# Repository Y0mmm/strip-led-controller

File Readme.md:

# STM8 RGB LED Strip Controller (Infrared NEC)

Custom low-cost RGB LED strip controller based on STM8, featuring Infrared (NEC protocol) control and perceptually-correct dimming.

## Overview

I bought a Paulmann SimpLED RGB strip to use as a bedside lamp. However, I was not satisfied with its functionalities (RGB light strobes before sleep didn’t make much sense), the colors were too aggressive for my eyes, and the dimming was linear (whereas human vision behaves more like a logarithmic response).

I initially wanted to reflash the original controller, but there were no markings on the IC package. So I decided to rebuild it from scratch.

This redesign addresses those issues with:
- Smooth, perceptually-correct brightness control
- Customizable color profiles
- Infrared remote compatibility (NEC protocol)
- Minimal, low-cost hardware

### Features

- Customizable color mapping
- Smooth, perceptually-correct brightness control
- Customizable color functions (ie: go-to-bed that slowly switch off the lights)
- Drop-in replacement PCB for original enclosure

## Hardware
### PCB Design
The PCB form factor and the position of the power barrel connector are designed to fit into the original controller enclosure and to be powered with the original 12VDC power supply.
I chose to use an STM8S001, as it is inexpensive, low-power, and more than sufficient for this project.

PCB design files are available in the PCB/ directory (KiCad).

### Preview

### Materials
|Name | Value | 	Number	| Comments|
| --- | ----- | ----------- | --------|
|STM8S001J3M3 |	|	1	|https://fr.farnell.com/stmicroelectronics/stm8s001j3m3/mcu-8bit-16mhz-nsoic-8/dp/4036166|
|MC78M05CDTRKG| | 		1|	7805 LDO regulator https://fr.farnell.com/on-semiconductor/mc78m05cdtrkg/regulateur-de-tension/dp/1703354|
|IRLML6344TRPBF	||	3	|N-channel MOSFETs used to control the LEDs https://fr.farnell.com/infineon/irlml6344trpbf/mosfet-canal-n-30v-6-3a-sot23/dp/1857299|
|MJ-179PH|	|	1|	Barrel power connector https://fr.farnell.com/multicomp-pro/mj-179ph/embase-basse-tension-12vdc-4a/dp/1737246|
|TSOP18438	|	|1|	IR receiver (replacement for the original one I broke — this one is actually more powerful) https://fr.farnell.com/vishay/tsop18438/recepteur-ir-24m-0-12mw-m2-lateral/dp/2889952|
|C1|	100 nF	|1|	1608 SMD|
|CVCAP	|1 µF	|1|	1608 SMD|
|R1, R2, R3	|1 kΩ|	3	|Load resistors for the MOSFETs, 1608 SMD|
|R4, R5, R6	|47 kΩ|	3	|Pull-down resistors, 1608 SMD|
|R7, R8, R9	|550 Ω|	3	|Optional load resistors for the LEDs, 1608 SMD|
|R10|	47 kΩ|	1	|Optional pull-down resistor for the JEXT button (not implemented)|
|R11|	1 kΩ	|1|	Load resistor for the optional JEXT button|
|RGB LEDs|	R, G, B|	3|	Optional, for debugging without the LED strip connected, 2012 SMD|
|Pin headers	|	|4	|Used for SWIM programming, IR receiver connection, and LED strip connection|

### IR remote buttons mapping : 

For all the buttons, the NEC Address is `0xef00`. The commands are the following:
| Col A  | Col B  | Col C  | Col D  |
| ------ | ------ | ------ | ------ |
| `0x00` | `0x01` | `0x02` | `0x03` |
| `0x04` | `0x05` | `0x06` | `0x07` |
| `0x08` | `0x09` | `0x0a` | `0x0b` | 
| `0x0c` | `0x0d` | `0x0e` | `0x0f` | 
| `0x10` | `0x11` | `0x12` | `0x13` | 
| `0x14` | `0x15` | `0x16` | `0x17` | 

## Firmware
I wrote the NEC infrared decoder from scratch, mainly for fun. It is built around a finite state machine. The command handler is implemented as a large switch statement.

The firmware is interrupt-driven, aiming to minimize power consumption (although it is not battery-powered).

You can add your own colors in src/config/led_config.c, adjust command codes to match your remote control, and implement additional features.

Since the STM8S001 does not include an FPU, all arithmetic is done using fixed-point math.

I used OpenAI Codex at the end to help refactor parts of the code.

### TODO
Implement features using a button connected to JEXT (e.g., on/off)

### Compile
I use SDCC for compilation. 
usage :
`make clean && make`

flash: I used a stlinkv2 with a SWIM Connector
`make flash`

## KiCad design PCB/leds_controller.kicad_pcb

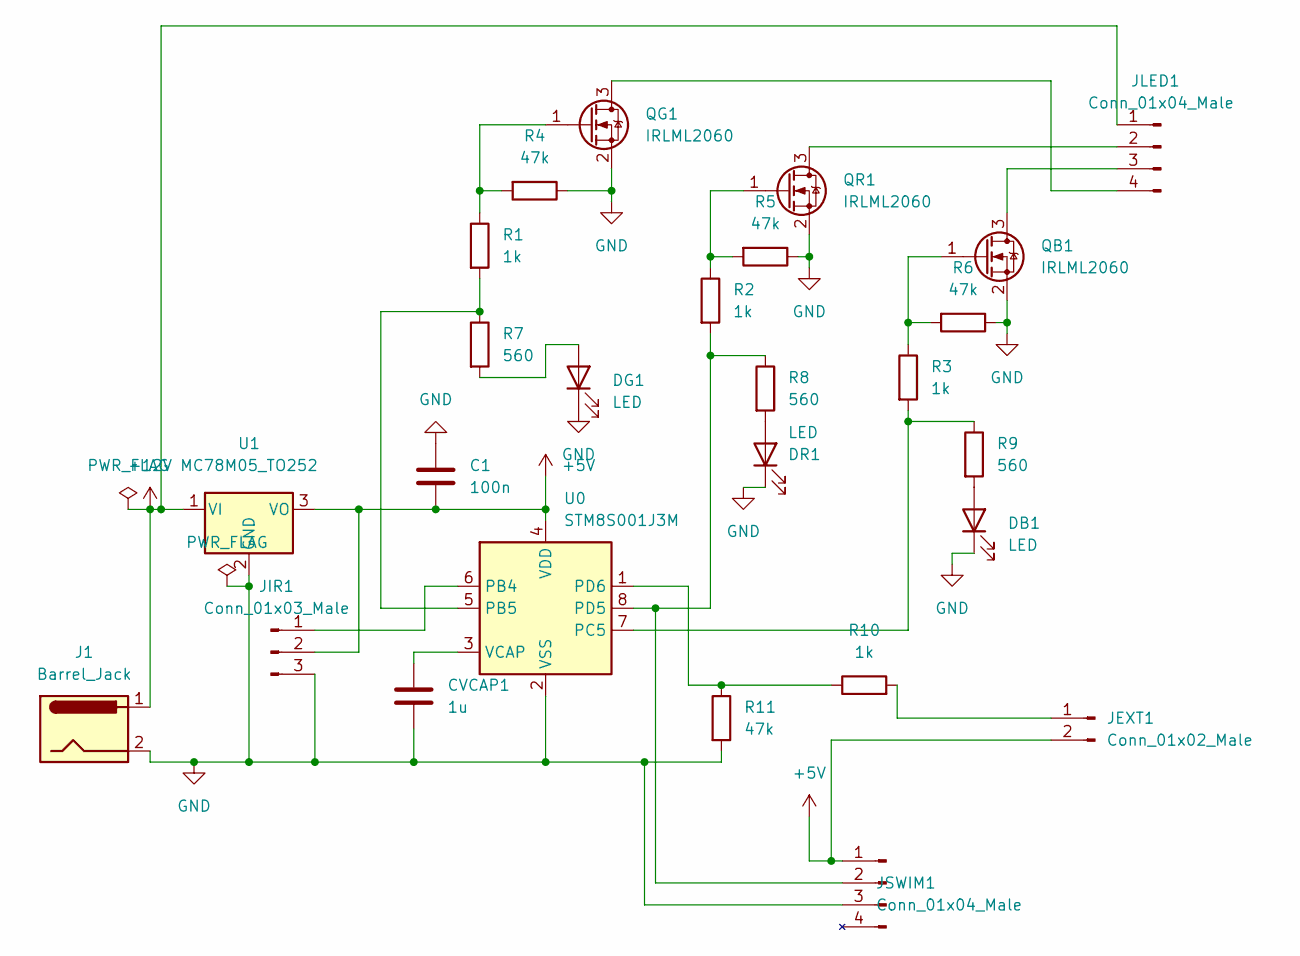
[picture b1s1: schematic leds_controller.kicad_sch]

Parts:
C1: 100n; C_0603_1608Metric
CVCAP1: 1u; C_0603_1608Metric
DB1: LED; LED_0805_2012Metric
DG1: LED; LED_0805_2012Metric
DR1: LED; LED_0805_2012Metric
J1: Barrel_Jack; BarrelJack_MJ-179PH
JEXT1: Conn_01x02_Male; PinHeader_1x02_P2.54mm_Vertical
JIR1: Conn_01x03_Male; PinHeader_1x03_P2.54mm_Vertical
JLED1: Conn_01x04_Male; PinHeader_1x04_P2.54mm_Vertical
JSWIM1: Conn_01x04_Male; PinHeader_1x04_P2.54mm_Vertical
QB1: IRLML2060; SOT-23
QG1: IRLML2060; SOT-23
QR1: IRLML2060; SOT-23
R1, R2, R3, R10: 1k; R_0603_1608Metric
R4, R5, R6, R11: 47k; R_0603_1608Metric
R7, R8, R9: 560; R_0603_1608Metric
U0: STM8S001J3M; SO-8_3.9x4.9mm_P1.27mm
U1: MC78M05_TO252; TO-252-2

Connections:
+5V: C1.2, JEXT1.2, JIR1.2, JSWIM1.1, U0.4 (VDD), U1.3 (VO)
+12V: J1.1, JLED1.1, U1.1 (VI)
GND: C1.1, CVCAP1.2, DB1.1 (K), DG1.1 (K), DR1.1 (K), J1.2, JIR1.3, JSWIM1.3, QB1.2 (S), QG1.2 (S), QR1.2 (S), R4.1, R5.1, R6.1, R11.2, U0.2 (VSS), U1.2 (GND)
unnamed: DB1.2 (A), R9.2
unnamed: DG1.2 (A), R7.2
unnamed: DR1.2 (A), R8.2
unnamed: JEXT1.1, R10.2
unnamed: JIR1.1, U0.6 (PB4)
unnamed: JLED1.2, QR1.3 (D)
unnamed: JLED1.3, QB1.3 (D)
unnamed: JLED1.4, QG1.3 (D)
unnamed: JSWIM1.2, R2.2, R8.1, U0.8 (PD5)
unnamed: QB1.1 (G), R3.1, R6.2
unnamed: QG1.1 (G), R1.1, R4.2
unnamed: QR1.1 (G), R2.1, R5.2
unnamed: R1.2, R7.1, U0.5 (PB5)
unnamed: R3.2, R9.1, U0.7 (PC5)
unnamed: R10.1, R11.1, U0.1 (PD6)
unnamed: CVCAP1.1, U0.3 (VCAP)

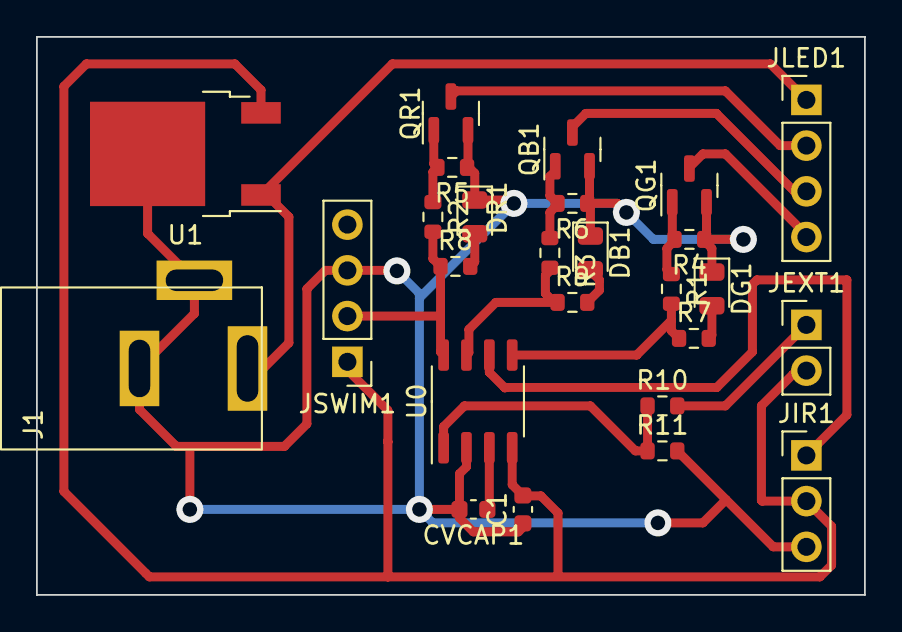
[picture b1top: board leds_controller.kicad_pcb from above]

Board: 2 copper layers, 46.0 x 31.0 mm, 26 parts (0 on the bottom side), 19 nets.

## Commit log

2026-04-22 V1.0
2026-04-23 updating to kicad 10, including 3D models screenshots
2026-04-26 updated doc
